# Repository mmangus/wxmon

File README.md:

# wxmon
Weather monitor using the ESP12E MCU and BME280 environmental sensor, comprised of an outdoor solar-powered sensor module and an indoor eInk display module. Optimized for low power consumption, draws only ~30μA while sleeping.

## Sensor module

### Progress
- [X] Schematic
- [X] PCB Layout
- [X] Gerber CAM files (zipped up and ready to upload to JLC PCB, OSH Park, etc)
- [ ] Software created using PlatformIO/Arduino - WIP
- [ ] Enclosure STL files

## Display module
### Progress
- [ ] Schematic
- [ ] PCB Layout
- [ ] Gerber CAM files (zipped up and ready to upload to JLC PCB, OSH Park, etc)
- [ ] Software created using PlatformIO/Arduino
- [ ] Enclosure STL files

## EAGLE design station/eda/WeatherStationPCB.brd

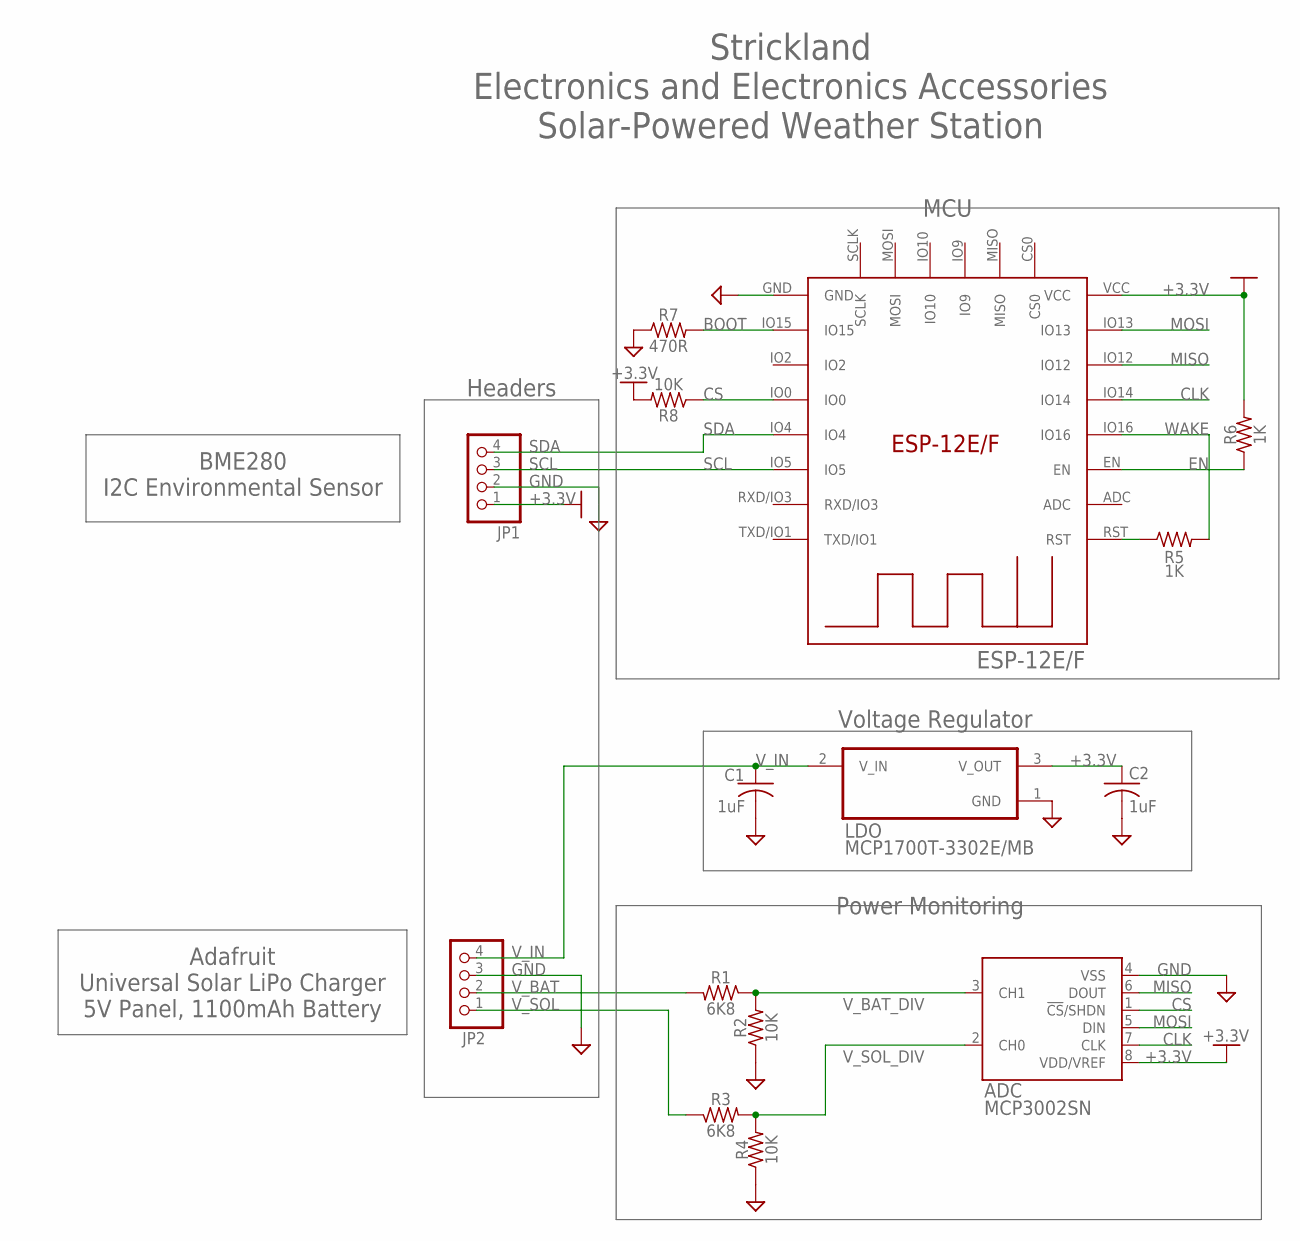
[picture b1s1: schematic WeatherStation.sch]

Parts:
ADC: MCP3002SN; SO-08
C1, C2: 1uF; CAPC2012X110
IC1: ESP-12E/F; ESP-12E
JP1: PINHD-1X4; 1X04
JP2: PINHD-1X4/90; 1X04/90
LDO: MCP1700T-3302E/MB; REG-MCP1700TA-4P6X2P6-3SM-H1P6
R1, R3: 6K8; RESC2012X65
R2, R4, R8: 10K; RESC2012X65
R5, R6: 1K; RESC2012X65
R7: 470R; RESC2012X65

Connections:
+3.3V: ADC.8 (VDD/VREF), C2.1, IC1.VCC, JP1.1, LDO.3 (V_OUT), R6.2, R8.2
BOOT: IC1.IO15, R7.2
CLK: ADC.7 (CLK), IC1.IO14
CS: ADC.1 (!CS!/SHDN), IC1.IO0, R8.1
EN: IC1.EN, R6.1
GND: ADC.4 (VSS), C1.2, C2.2, IC1.GND, JP1.2, JP2.3, LDO.1 (GND), R2.1, R4.1, R7.1
MISO: ADC.6 (DOUT), IC1.IO12
MOSI: ADC.5 (DIN), IC1.IO13
RST: IC1.RST, R5.1
SCL: IC1.IO5, JP1.3
SDA: IC1.IO4, JP1.4
V_BAT: JP2.2, R1.2
V_BAT_DIV: ADC.3 (CH1), R1.1, R2.2
V_IN: C1.1, JP2.4, LDO.2 (V_IN)
V_SOL: JP2.1, R3.1
V_SOL_DIV: ADC.2 (CH0), R3.2, R4.2
WAKE: IC1.IO16, R5.2

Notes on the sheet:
Voltage Regulator
Power Monitoring
MCU
Headers
Strickland Electronics and Electronics Accessories Solar-Powered Weather Station
BME280 I2C Environmental Sensor
Adafruit Universal Solar LiPo Charger 5V Panel, 1100mAh Battery

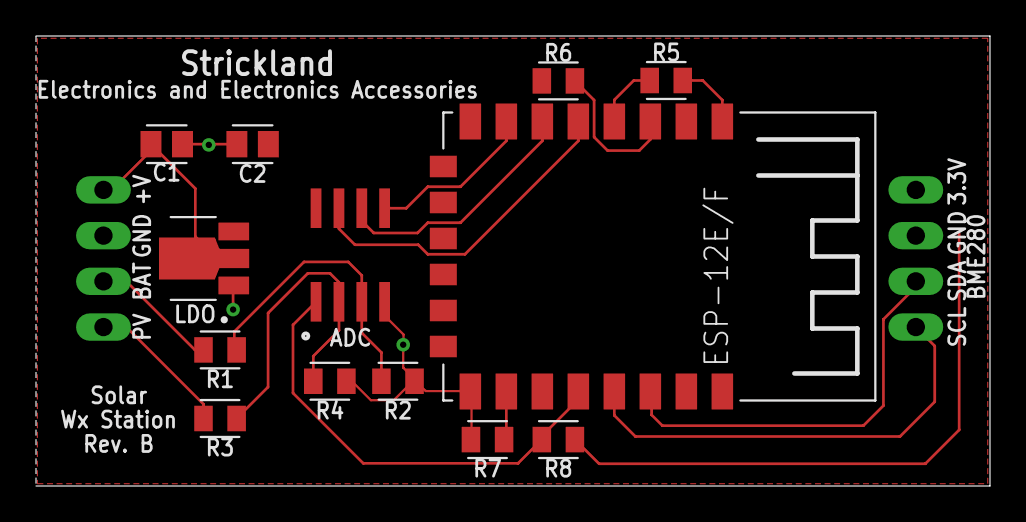
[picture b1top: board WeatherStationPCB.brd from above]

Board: 2 copper layers, 53.0 x 25.0 mm, 15 parts (0 on the bottom side), 17 nets.

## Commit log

2020-12-29 update for rev B
